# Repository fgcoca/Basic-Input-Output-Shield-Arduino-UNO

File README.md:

# **Escudo de entradas y salidas básicas para Arduino UNO**
# **(Basic Input Output Shield)**
Migración del Escudo de entradas y salidas básicas para Arduino UNO (Basic Input Output Shield) creado por Domingo Llorente del Departamento de Electrónica del IES Luis de Lucena de Guadalajara.

En las imágenes vemos una vista 3D del diseño en KiCAD y el aspecto real de la placa.

Captura | Fotografa
-- | --
![Imagen 1][1] | ![Imagen 2][2]

[1]: https://github.com/fgcoca/Basic-Input-Output-Shield-Arduino-UNO/blob/master/images/captura-m.png
[2]: https://github.com/fgcoca/Basic-Input-Output-Shield-Arduino-UNO/blob/master/images/4x7segment-on-board-m.png

## **Diseño de la PCB** 

En el enlace están todos los archivos KiCAD por si te apetece ver cómo se ha realizado el diseño de esta bonita Shield.

[BIOS_Shield_1.0_Migration](https://github.com/fgcoca/Basic-Input-Output-Shield-Arduino-UNO/tree/master/BIOS_Shield_1.0_Migration)

## **Memorias** 

* [Original en pdf](https://github.com/fgcoca/Basic-Input-Output-Shield-Arduino-UNO/blob/master/Manuales/original/BIOS_Shield_memoria_rev1.2.pdf)
* [Migrada en odt](https://github.com/fgcoca/Basic-Input-Output-Shield-Arduino-UNO/blob/master/Manuales/migrado/BIOS_Shield_migration_memory_rev1.0.odt)
* [Migrada en pdf](https://github.com/fgcoca/Basic-Input-Output-Shield-Arduino-UNO/blob/master/Manuales/migrado/BIOS_Shield_migration_memory_rev1.0.pdf)
* [Directorio de imágenes](https://github.com/fgcoca/Basic-Input-Output-Shield-Arduino-UNO/tree/master/images)

## **Programas para prueba de funcionalidad** 

* [Todo en un zip](https://github.com/fgcoca/Basic-Input-Output-Shield-Arduino-UNO/blob/master/BIOS_Programas_Demo_v1/BIOS_Programas_Demo_y_librerias.zip)
* [Directorio de sketches individuales y librerias](https://github.com/fgcoca/Basic-Input-Output-Shield-Arduino-UNO/tree/master/BIOS_Programas_Demo_v1)

## **Descripción del uso de pines** 

En el enlace tenemos los archivos svg y pdf del pinout de la PCB. El svg se facilita por si te apetece ver cómo se hace de forma sencilla un pinout en Inkscape.

* [Pinout en svg](https://github.com/fgcoca/Basic-Input-Output-Shield-Arduino-UNO/blob/master/pinout/BIOS_Shield_1.0_Migration.svg)
* [Pinout en pdf](https://github.com/fgcoca/Basic-Input-Output-Shield-Arduino-UNO/blob/master/pinout/BIOS_Shield_1.0_Migration.pdf)

## **Soporte 3D para el display de 4x7 segmentos** 

Directorio con el archivo FreeCAD de diseño del soporte y dos versiones stl del mismo.

* [Soporte](https://github.com/fgcoca/Basic-Input-Output-Shield-Arduino-UNO/tree/master/soporte)

### **Autor**

[Federico Coca Caba] (https://github.com/fgcoca)

### **Licencia**
<br /> <a rel="license" href="http://creativecommons.org/licenses/by-sa/4.0/">Creative Commons Attribution-ShareAlike 4.0 International License</a>.

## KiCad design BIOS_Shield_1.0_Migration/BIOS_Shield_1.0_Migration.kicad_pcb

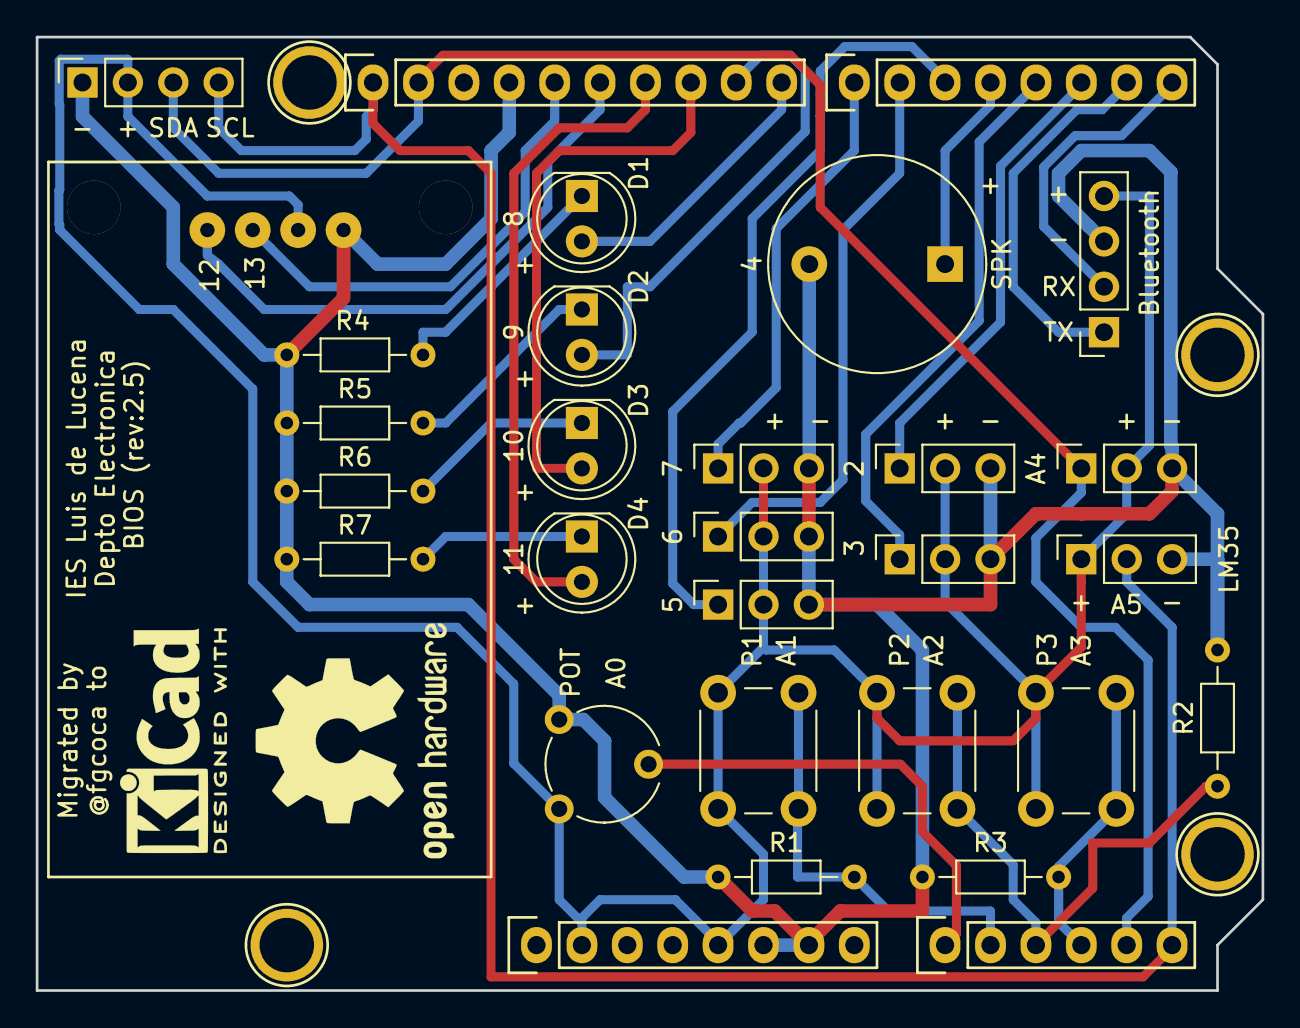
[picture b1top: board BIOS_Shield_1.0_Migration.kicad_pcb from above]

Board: 2 copper layers, 68.6 x 53.3 mm, 34 parts (0 on the bottom side), 26 nets.

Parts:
D1, D2, D3, D4: LED; LED_D5.0mm
J1: Power; Socket_Strip_Arduino_1x08
J2: Analog; Socket_Strip_Arduino_1x06
J3: Digital; Socket_Strip_Arduino_1x10
J4: Digital; Socket_Strip_Arduino_1x08
J5: CONN-LCD_I2C; PinSocket_1x04_P2.54mm_Vertical
J6: Bluetooth; PinSocket_1x04_P2.54mm_Vertical
J7: DISPLAY X4; TM1637
J8, J9, J10, J11, J12, J13: Conn_01x03; PinSocket_1x03_P2.54mm_Vertical
LM35: Conn_01x03; PinSocket_1x03_P2.54mm_Vertical
P1, P2, P3: SW_Push; SW_PUSH_6mm
P5, P6, P7, P8: CONN_01X01; Arduino_1pin
POT: R_POT; Potentiometer_Piher_PT-6-V_Vertical
R1, R2, R3: 10k; R_Axial_DIN0204_L3.6mm_D1.6mm_P7.62mm_Horizontal
R4, R5, R6, R7: 1k; R_Axial_DIN0204_L3.6mm_D1.6mm_P7.62mm_Horizontal
SPK: Buzzer; Buzzer_12x9.5RM7.6

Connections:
+5V: J1.2, J1.5, J5.2, J6.4, J7.2, J8.2, J9.2, J10.2, J11.2, J12.2, J13.2, LM35.1, P1.1, P2.1, P3.1, POT.1
/0(Rx): J4.8, J6.2
/1(Tx): J4.7, J6.1
/2: J4.6, J9.1
/3(**): J4.5, J11.1
/4: J4.4, SPK.1
/5(**): J4.3, J12.1
/6(**): J4.2, J8.1
/7: J4.1, J13.1
/8: D1.2, J3.10
/9(**): D2.2, J3.9
/10(**/SS): D3.2, J3.8
/11(**/MOSI): D4.2, J3.7
/12(MISO): J3.6, J7.4
/13(SCK): J3.5, J7.3
/A0: J2.1, POT.2
/A1: J2.2, P1.2, R1.2
/A2: J2.3, P2.2, R2.2
/A3: J2.4, P3.2, R3.2
/A4(SDA): J2.5, J3.2, J5.3, J10.1
/A5(SCL): J2.6, J3.1, J5.4, LM35.2
GND: J1.6, J1.7, J3.4, J5.1, J6.3, J7.1, J8.3, J9.3, J10.3, J11.3, J12.3, J13.3, LM35.3, POT.3, R1.1, R2.1, R3.1, R4.2, R5.2, R6.2, R7.2, SPK.2
unnamed: D1.1, R4.1
unnamed: D2.1, R5.1
unnamed: D3.1, R6.1
unnamed: D4.1, R7.1
